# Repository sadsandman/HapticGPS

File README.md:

# HapticGPS — Wearable Haptic Navigation Board

A compact 4-layer wearable PCB that delivers directional haptic feedback via a piezoelectric actuator. The board combines a Bluetooth Low Energy SoC, a 6-axis IMU, a piezoelectric haptic driver, non-volatile FRAM storage, and a LiPo power management IC — all in a **30 × 33 mm** footprint.

---

## PCB Views

| Top | Bottom |
|:---:|:---:|
|  |  |

---

## Key Features

- **Ultra-low-power BLE 5.4** SoC (Nordic nRF54L15) with on-board PCB trace antenna
- **Piezoelectric haptic feedback** driven by a dedicated high-voltage driver IC (Bosch BOS1921)
- **6-axis IMU** (ST LSM6DSV) for orientation and motion sensing
- **8 Mbit FRAM** (Cypress CY15B108QN) for fast, wear-unlimited non-volatile storage
- **Integrated LiPo charger + dual DCDC + LDO** (Nordic nPM1300 PMIC)
- **4-layer stackup** for clean power planes and antenna isolation
- SWD debug/programming header

---

## Hardware Specifications

| Parameter | Value |
|---|---|
| PCB size | 30 × 33 mm |
| Stackup | 4-layer (F.Cu / In1.Cu / In2.Cu / B.Cu) |
| Board thickness | 1.526 mm |
| Design tool | KiCad 9.0 |
| Revision | V1.0.0 |

---

## Block Diagram

---

## Bill of Materials (Key ICs)

| Ref | Part | Description |
|-----|------|-------------|
| U1 | [Nordic nPM1300](https://www.nordicsemi.com/Products/nPM1300) | PMIC — LiPo charger, dual buck, LDO |
| U2 | [Nordic nRF54L15-QFAA-R](https://www.nordicsemi.com/Products/nRF54L15) | BLE 5.4 SoC, Arm Cortex-M33 |
| U3 | [Bosch BOS1921CQR](https://www.bosch-sensortec.com) | Piezoelectric haptic driver |
| U4 | [Cypress CY15B108QN](https://www.infineon.com/cms/en/product/memories/f-ram-ferroelectric-ram/serial-f-ram/cy15b108qn/) | 8 Mbit SPI FRAM |
| IC1 | [ST LSM6DSV80XTR](https://www.st.com/en/mems-and-sensors/lsm6dsv80x.html) | 6-axis IMU (accel + gyro) |
| Y1/Y2 | Crystal | MCU system & RTC clock references |

---

## Connectors & Interfaces

| Designator | Function | Signals |
|---|---|---|
| J3 | SWD debug header | VIN, RST, DIO, CLK, GND |
| J4 | LiPo battery | VBAT, NTC, GND |
| J2 | Piezo actuator | PZP, PZN |

---

## Getting Started

### Prerequisites

- [KiCad 9.0+](https://www.kicad.org/) to open schematics and PCB layout
- A LiPo cell (connected via J4)
- A piezoelectric actuator (connected via J2)
- An SWD programmer (e.g. J-Link, nRF9160 DK) for firmware flashing

### Opening the Project

```bash
git clone <repo-url>
cd HapticGPS/HapticGPS
kicad HapticGPS.kicad_pro
```

### Generating PCB Renders

Renders are generated with the KiCad CLI:

```bash
# Top view
kicad-cli pcb render \
  --output Doc/renders/top.png \
  --width 1600 --height 1200 \
  --side top --quality high --floor \
  HapticGPS/HapticGPS.kicad_pcb

# Bottom view
kicad-cli pcb render \
  --output Doc/renders/bottom.png \
  --width 1600 --height 1200 \
  --side bottom --quality high --floor \
  HapticGPS/HapticGPS.kicad_pcb

# Isometric view
kicad-cli pcb render \
  --output Doc/renders/iso.png \
  --width 1600 --height 1200 \
  --quality high --floor --perspective \
  --rotate "30,0,45" \
  HapticGPS/HapticGPS.kicad_pcb
```

---

## Repository Structure

```
HapticGPS/
├── HapticGPS/
│   ├── HapticGPS.kicad_pro       # KiCad project file
│   ├── HapticGPS.kicad_pcb       # PCB layout
│   ├── HapticGPS.kicad_sch       # Top-level schematic
│   └── modules/
│       ├── controller.sch.kicad_sch     # MCU + FRAM
│       ├── power.kicad_sch              # PMIC circuit
│       ├── piezoelectric_driver.kicad_sch  # Haptic driver
│       └── (imu.kicad_sch)              # IMU sub-sheet
└── Doc/
    ├── architecture/
    │   └── Basic_architecture.svg
    └── renders/
        ├── top.png
        ├── bottom.png
        └── iso.png
```

---

## License

This hardware design is released under the **CERN Open Hardware Licence Version 2 — Strongly Reciprocal (CERN-OHL-S v2)**.  
See [`LICENSE`](LICENSE) for the full text, or visit [ohwr.org/cern_ohl_s_v2.txt](https://ohwr.org/cern_ohl_s_v2.txt).

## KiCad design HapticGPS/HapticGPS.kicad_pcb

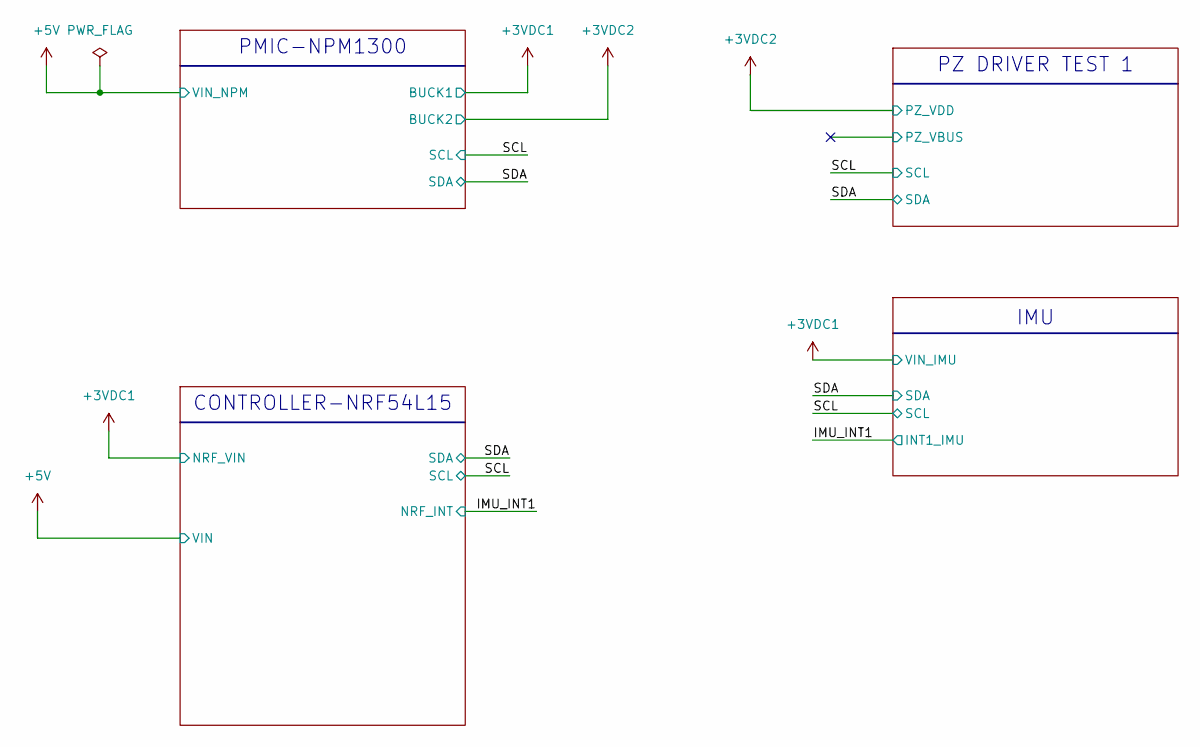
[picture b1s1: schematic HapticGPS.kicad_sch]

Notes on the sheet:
PMIC-NPM1300
IMU
PZ DRIVER TEST 1
CONTROLLER-NRF54L15

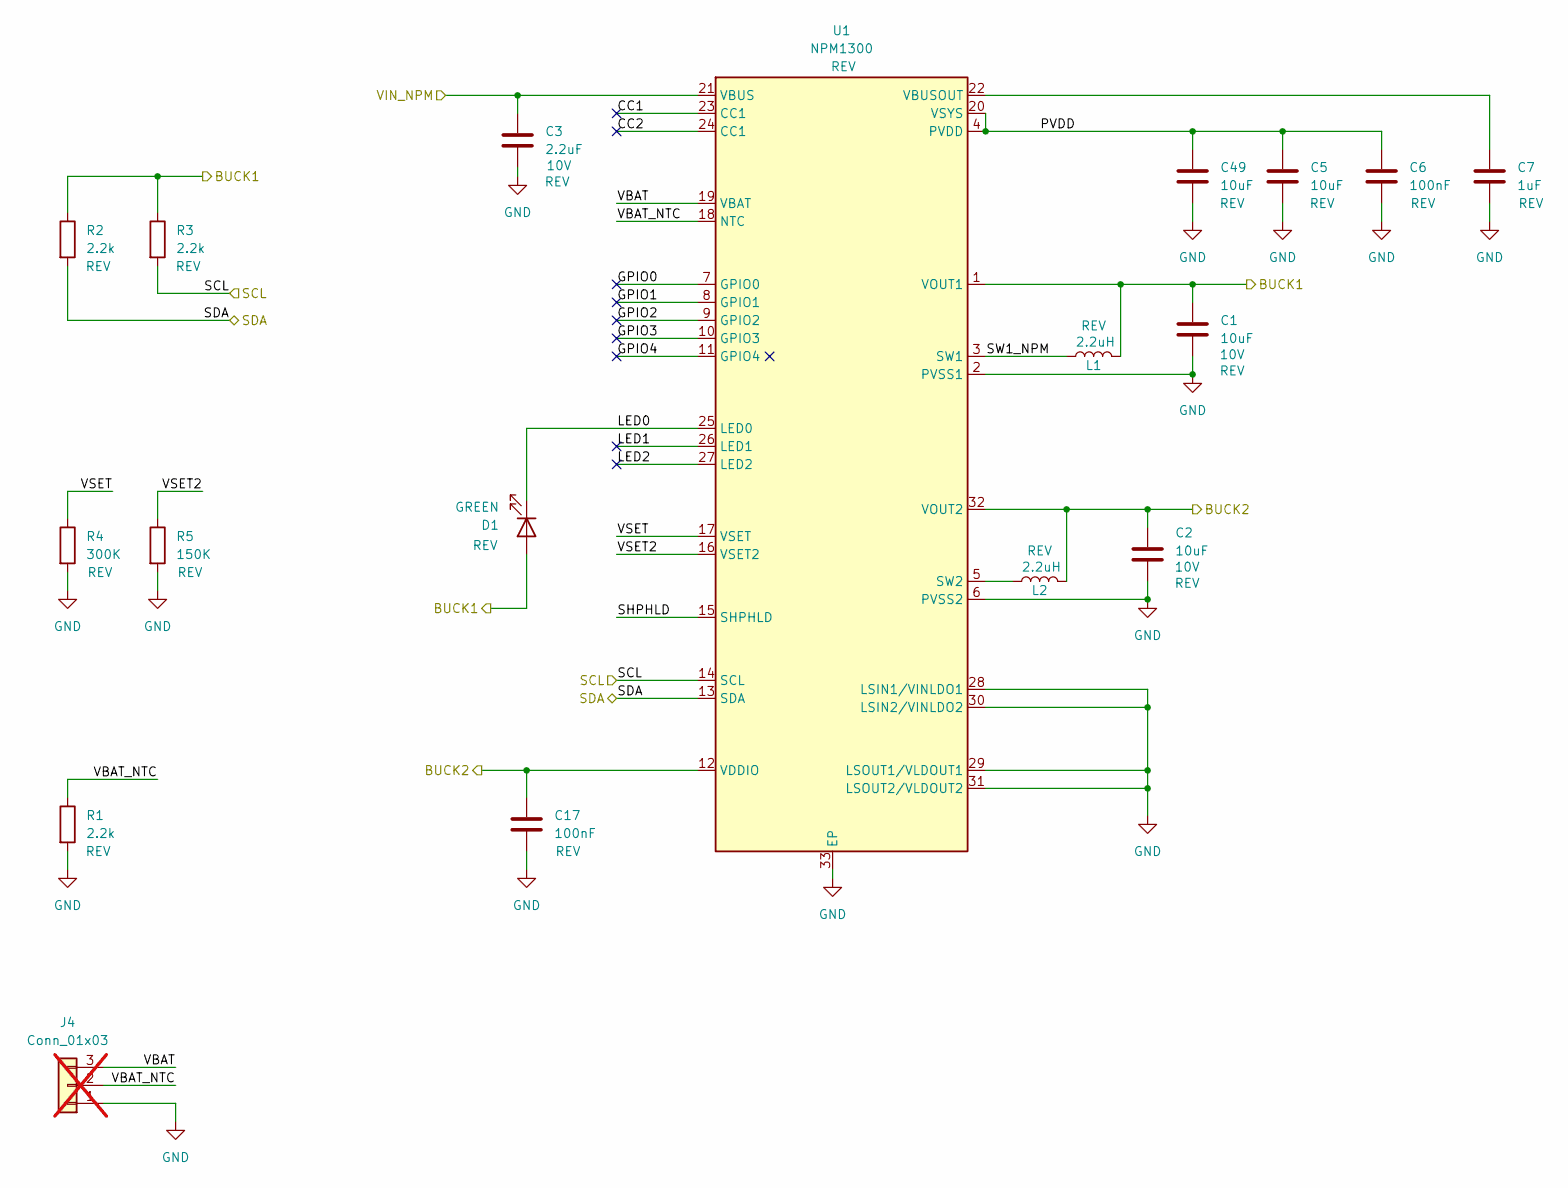
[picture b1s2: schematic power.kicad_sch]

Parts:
C1, C2: 10uF; C_0603_1608Metric; Voltage 10V
C3: 2.2uF; C_0402_1005Metric; Voltage 10V
C5, C49: 10uF; C_0603_1608Metric
C6, C17: 100nF; C_0402_1005Metric
C7: 1uF; C_0402_1005Metric
D1: GREEN; LED_0402_1005Metric
J4: Conn_01x03; 01x03_1.5x3; not fitted
L1, L2: 2.2uH; L_1008_2520Metric
R1, R2, R3: 2.2k; R_0603_1608Metric
R4: 300K; R_0402_1005Metric
R5: 150K; R_0402_1005Metric
U1: NPM1300; VQFN-32-1EP_5x5mm_P0.5mm_EP3.1x3.1mm_ThermalVias

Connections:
+3VDC1: C1.1, D1.2 (A), L1.2, R2.1, R3.1, U1.1 (VOUT1); also elsewhere on the board
+3VDC2: C2.1, C17.1, L2.2, U1.12 (VDDIO), U1.32 (VOUT2); also elsewhere on the board
+5V: C3.1, U1.21 (VBUS); also elsewhere on the board
/POWER/CC1: U1.23 (CC1)
/POWER/CC2: U1.24 (CC1)
/POWER/GPIO0: U1.7 (GPIO0)
/POWER/GPIO1: U1.8 (GPIO1)
/POWER/GPIO2: U1.9 (GPIO2)
/POWER/GPIO3: U1.10 (GPIO3)
/POWER/GPIO4: U1.11 (GPIO4)
/POWER/LED0: D1.1 (K), U1.25 (LED0)
/POWER/LED1: U1.26 (LED1)
/POWER/LED2: U1.27 (LED2)
/POWER/PVDD: C5.1, C6.1, C49.1, U1.4 (PVDD), U1.20 (VSYS)
/POWER/SHPHLD: U1.15 (SHPHLD)
/POWER/SW1_NPM: L1.1, U1.3 (SW1)
/POWER/VBAT: J4.3, U1.19 (VBAT)
/POWER/VBAT_NTC: J4.2, R1.1, U1.18 (NTC)
/POWER/VSET: R4.1, U1.17 (VSET)
/POWER/VSET2: R5.1, U1.16 (VSET2)
/SCL: R3.2, U1.14 (SCL); also elsewhere on the board
/SDA: R2.2, U1.13 (SDA); also elsewhere on the board
GND: C1.2, C2.2, C3.2, C5.2, C6.2, C7.2, C17.2, C49.2, J4.1, R1.2, R4.2, R5.2, U1.2 (PVSS1), U1.6 (PVSS2), U1.28 (LSIN1/VINLDO1), U1.29 (LSOUT1/VLDOUT1), U1.30 (LSIN2/VINLDO2), U1.31 (LSOUT2/VLDOUT2), U1.33 (EP); also elsewhere on the board
unnamed: L2.1, U1.5 (SW2)
unnamed: C7.1, U1.22 (VBUSOUT)

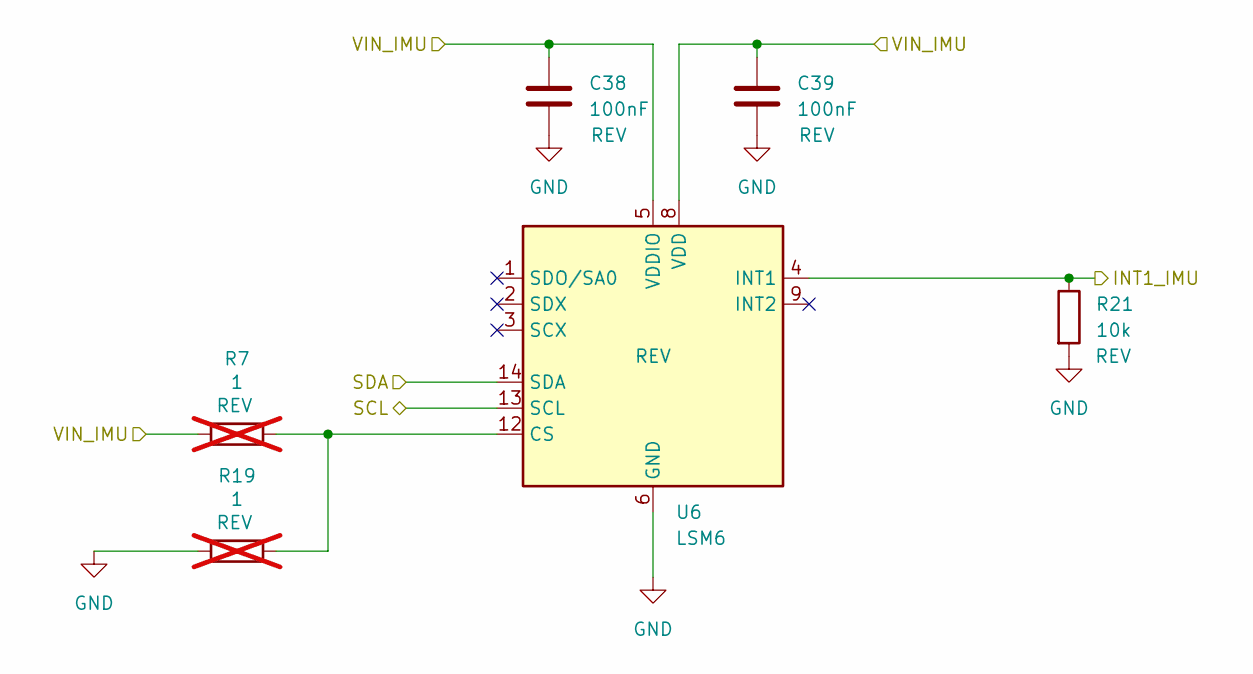
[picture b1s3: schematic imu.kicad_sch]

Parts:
C38, C39: 100nF; C_0402_1005Metric
R7, R19: 1; R_0402_1005Metric; not fitted
R21: 10k; R_0402_1005Metric
U6: LSM6; LGA-14_3x2.5mm_P0.5mm_LayoutBorder3x4y

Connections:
+3VDC1: C38.1, C39.1, R7.1, U6.5 (VDDIO), U6.8 (VDD); also elsewhere on the board
/IMU_INT1: R21.1, U6.4 (INT1); also elsewhere on the board
/SCL: U6.13 (SCL); also elsewhere on the board
/SDA: U6.14 (SDA); also elsewhere on the board
GND: C38.2, C39.2, R19.1, R21.2, U6.6 (GND), U6.7 (GND); also elsewhere on the board
unnamed: R7.2, R19.2, U6.12 (CS)

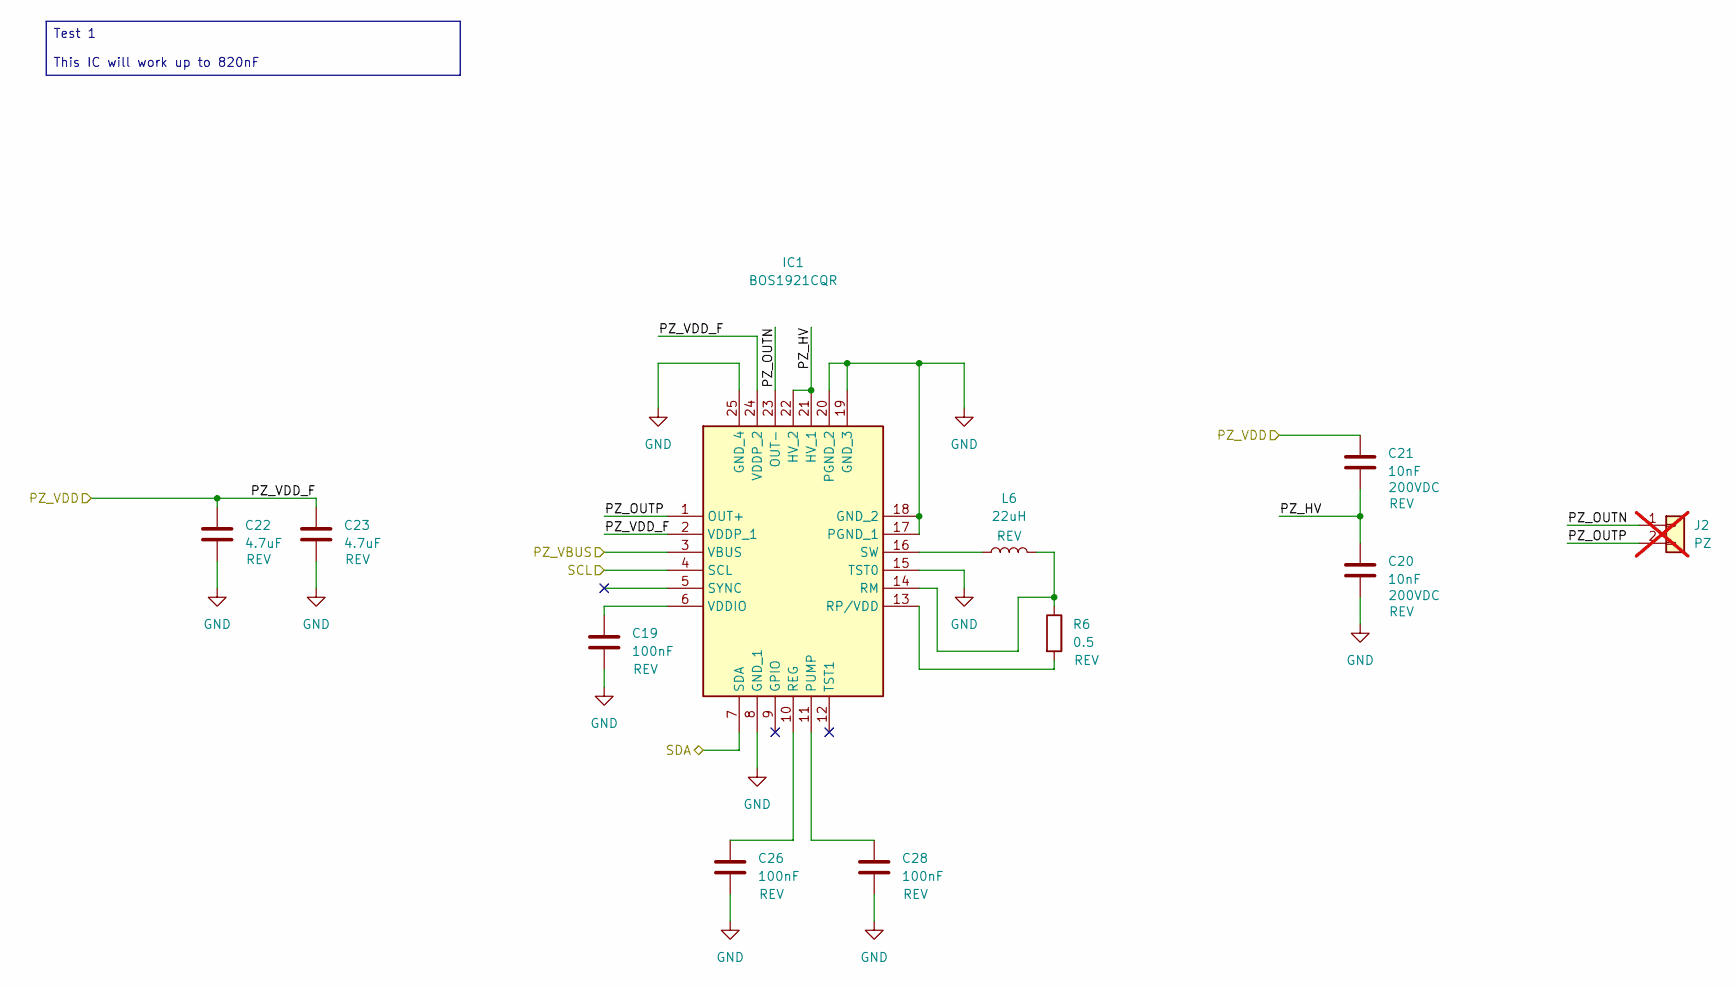
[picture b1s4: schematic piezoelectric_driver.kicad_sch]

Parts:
C19: 100nF; C_0603_1608Metric
C20, C21: 10nF; C_0603_1608Metric; Voltage 200VDC
C22, C23: 4.7uF; C_0603_1608Metric
C26, C28: 100nF; C_0402_1005Metric
IC1: BOS1921CQR; VQFN-24-1EP_4x4mm_P0.5mm_EP2.45x2.45mm_ThermalVias
J2: PZ; PinSocket_1x02_P2.00mm_Vertical; not fitted
L6: 22uH; L_Taiyo-Yuden_MD-5050
R6: 0.5; R_0805_2012Metric

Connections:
+3VDC2: C21.1, C22.2, C23.2, IC1.2 (VDDP_1), IC1.24 (VDDP_2); also elsewhere on the board
/PIEZOELECTRIC DRIVER/PZ_HV: C20.1, C21.2, IC1.21 (HV_1), IC1.22 (HV_2)
/PIEZOELECTRIC DRIVER/PZ_OUTN: IC1.23 (OUT-), J2.1
/PIEZOELECTRIC DRIVER/PZ_OUTP: IC1.1 (OUT+), J2.2
/PIEZOELECTRIC DRIVER/PZ_VBUS: IC1.3 (VBUS)
/SCL: IC1.4 (SCL); also elsewhere on the board
/SDA: IC1.7 (SDA); also elsewhere on the board
GND: C19.2, C20.2, C22.1, C23.1, C26.2, C28.2, IC1.8 (GND_1), IC1.15 (TST0), IC1.17 (PGND_1), IC1.18 (GND_2), IC1.19 (GND_3), IC1.20 (PGND_2), IC1.25 (GND_4); also elsewhere on the board
unnamed: C28.1, IC1.11 (PUMP)
unnamed: C26.1, IC1.10 (REG)
unnamed: IC1.14 (RM), L6.2, R6.1
unnamed: IC1.13 (RP/VDD), R6.2
unnamed: IC1.16 (SW), L6.1
unnamed: C19.1, IC1.6 (VDDIO)

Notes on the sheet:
Test 1 This IC will work up to 820nF

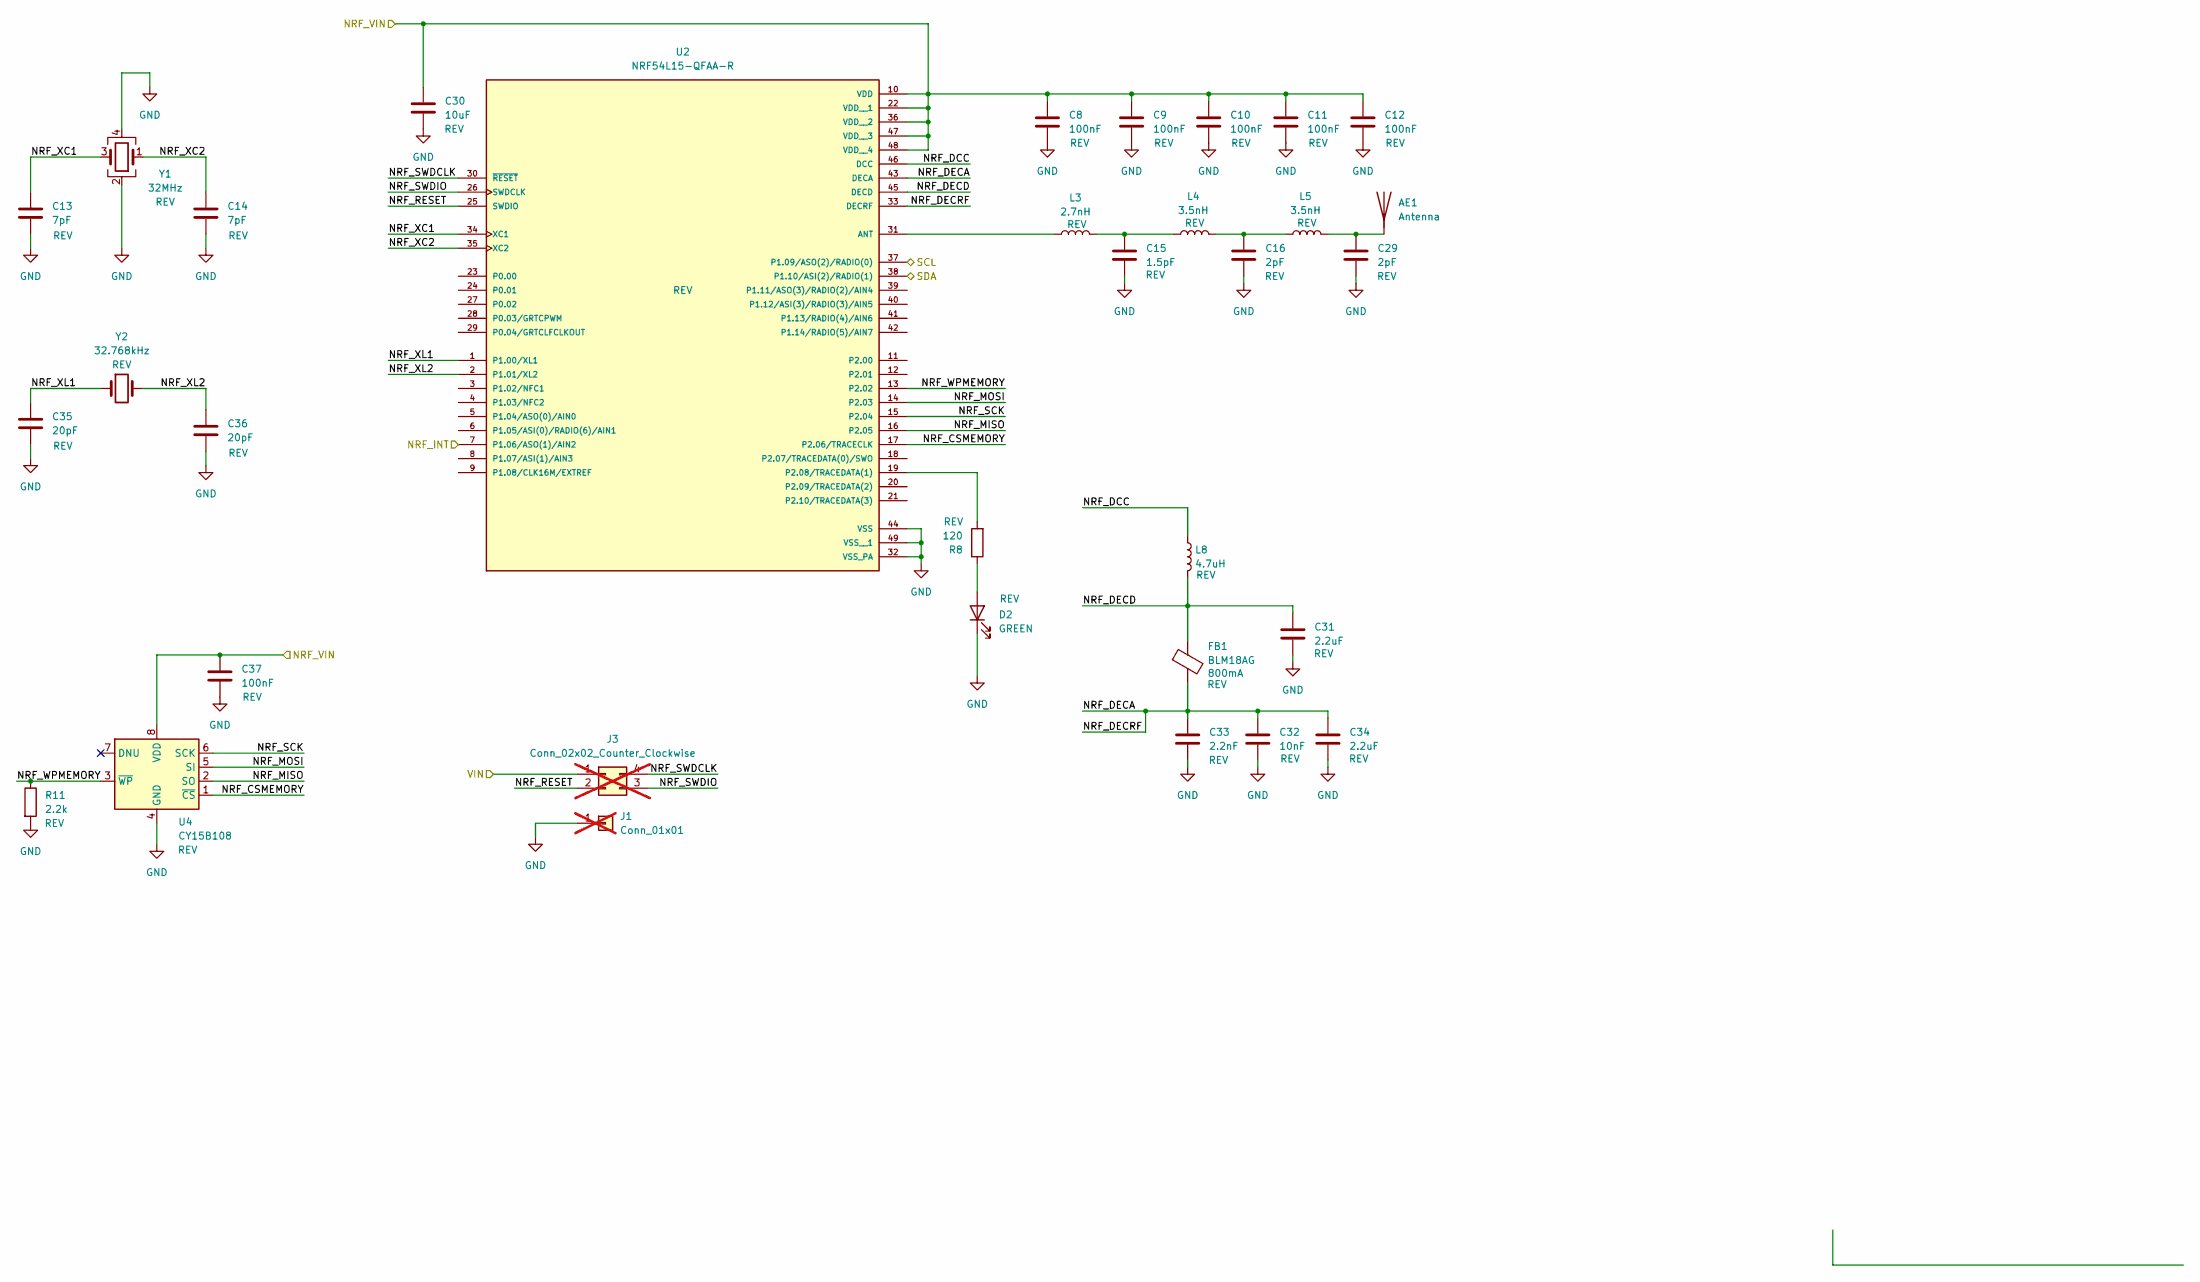
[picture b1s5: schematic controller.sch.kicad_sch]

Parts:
AE1: Antenna; Texas_SWRA117D_2.4GHz_Left
C8, C9, C10, C11, C12: 100nF; C_0402_1005Metric
C13, C14: 7pF; C_0402_1005Metric
C15: 1.5pF; C_0402_1005Metric
C16, C29: 2pF; C_0402_1005Metric
C30: 10uF; C_0805_2012Metric
C31, C34: 2.2uF; C_0402_1005Metric
C32: 10nF; C_0402_1005Metric
C33: 2.2nF; C_0402_1005Metric
C35, C36: 20pF; C_0402_1005Metric
C37: 100nF; C_0603_1608Metric
D2: GREEN; LED_0402_1005Metric
FB1: BLM18AG; L_0603_1608Metric
J1: Conn_01x01; PinHeader_1x01_P2.00mm_Vertical; not fitted
J3: Conn_02x02_Counter_Clockwise; not fitted
L3: 2.7nH; L_0402_1005Metric
L4, L5: 3.5nH; L_0402_1005Metric
L8: 4.7uH; L_0603_1608Metric
R8: 120; R_0402_1005Metric
R11: 2.2k; R_0603_1608Metric
U2: NRF54L15-QFAA-R; QFN-48-1EP_6x6mm_P0.4mm_EP4.6x4.6mm_ThermalVias; PARTREV 0.8
U4: CY15B108; SOIC-8_5.3x5.3mm_P1.27mm
Y1: 32MHz; Crystal_SMD_2016-4Pin_2.0x1.6mm
Y2: 32.768kHz; Crystal_SMD_2012-2Pin_2.0x1.2mm

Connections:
+3VDC1: C8.1, C9.1, C10.1, C11.1, C12.1, C30.1, C37.1, U2.10 (VDD), U2.22 (VDD__1), U2.36 (VDD__2), U2.47 (VDD__3), U2.48 (VDD__4), U4.8 (VDD); also elsewhere on the board
+5V: J3.1; also elsewhere on the board
/CONTROLLER/NRF_CSMEMORY: U2.17 (P2.06/TRACECLK), U4.1 (~CS)
/CONTROLLER/NRF_DCC: L8.1, U2.46 (DCC)
/CONTROLLER/NRF_DECA: C32.1, C33.1, C34.1, FB1.2, U2.33 (DECRF), U2.43 (DECA)
/CONTROLLER/NRF_DECD: C31.1, FB1.1, L8.2, U2.45 (DECD)
/CONTROLLER/NRF_MISO: U2.16 (P2.05), U4.2 (SO)
/CONTROLLER/NRF_MOSI: U2.14 (P2.03), U4.5 (SI)
/CONTROLLER/NRF_RESET: J3.2, U2.25 (SWDIO)
/CONTROLLER/NRF_SCK: U2.15 (P2.04), U4.6 (SCK)
/CONTROLLER/NRF_SWDCLK: J3.4, U2.30 (~RESET)
/CONTROLLER/NRF_SWDIO: J3.3, U2.26 (SWDCLK)
/CONTROLLER/NRF_WPMEMORY: R11.1, U2.13 (P2.02), U4.3 (~WP)
/CONTROLLER/NRF_XC1: C13.1, U2.34 (XC1), Y1.3
/CONTROLLER/NRF_XC2: C14.1, U2.35 (XC2), Y1.1
/CONTROLLER/NRF_XL1: C35.1, U2.1 (P1.00/XL1), Y2.1
/CONTROLLER/NRF_XL2: C36.1, U2.2 (P1.01/XL2), Y2.2
/IMU_INT1: U2.7 (P1.06/ASO(1)/AIN2); also elsewhere on the board
/SCL: U2.37 (P1.09/ASO(2)/RADIO(0)); also elsewhere on the board
/SDA: U2.38 (P1.10/ASI(2)/RADIO(1)); also elsewhere on the board
GND: AE1.2, C8.2, C9.2, C10.2, C11.2, C12.2, C13.2, C14.2, C15.2, C16.2, C29.2, C30.2, C31.2, C32.2, C33.2, C34.2, C35.2, C36.2, C37.2, D2.1 (K), J1.1, R11.2, U2.32 (VSS_PA), U2.44 (VSS), U2.49 (VSS__1), U4.4 (GND), Y1.2, Y1.4; also elsewhere on the board
unnamed: AE1.1 (A), C29.1, L5.2
unnamed: C15.1, L3.2, L4.1
unnamed: C16.1, L4.2, L5.1
unnamed: D2.2 (A), R8.1
unnamed: L3.1, U2.31 (ANT)
unnamed: R8.2, U2.19 (P2.08/TRACEDATA(1))

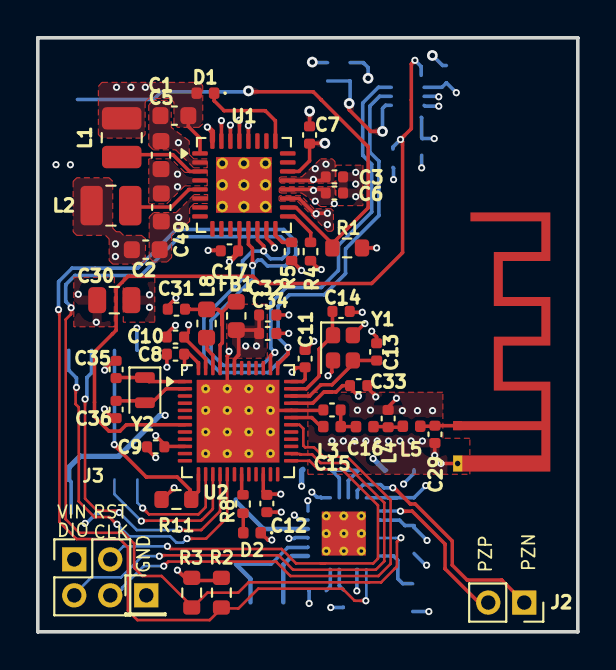
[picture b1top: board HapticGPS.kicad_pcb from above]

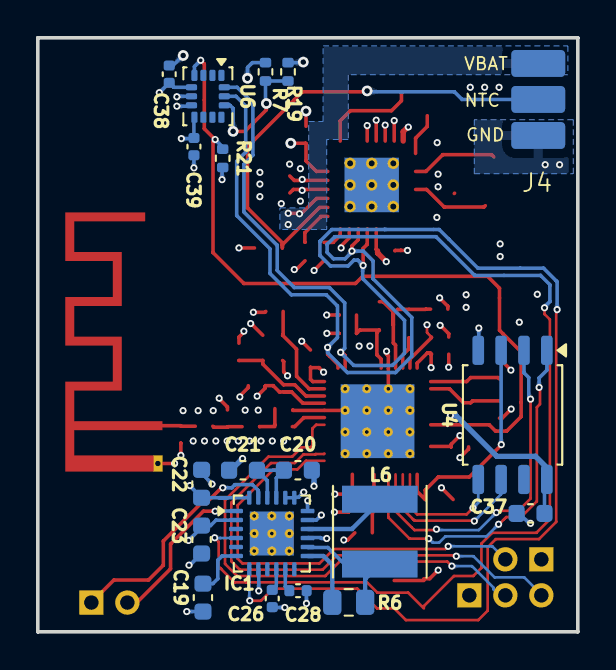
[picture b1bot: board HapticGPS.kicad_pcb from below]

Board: 4 copper layers, 30.0 x 33.0 mm, 68 parts (19 on the bottom side), 47 nets.

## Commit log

2026-04-30 updating
2026-05-24 save
2026-05-31 eliminating GPS, and second piezo driver
2026-05-31 add README, LICENSE, and PCB renders
    Includes raytraced top/bottom/isometric renders generated with kicad-cli,
    a full project README with board specs and BoM, and CERN-OHL-S v2 license.
2026-05-31 Correnting iso image
2026-05-31 update top and bottom PCB renders with new 3D models
2026-05-31 Corecting iso

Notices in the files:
README.md:
License: CERN-OHL-S v2
